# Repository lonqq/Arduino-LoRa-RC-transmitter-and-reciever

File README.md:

# Arduino based RC system
The ultimate DIY radio control system.
Remotely operate model airplanes, multicopters, boats, land vehicles, robots, or anything you can imagine.

## Main features
- 20 fully proportional RC channels, each channel encoded with 10 bits.
- Configurable RC channel output signal format.
- Update rate of 50x per second for all RC channels.
- Receiver binding, Adjustable RF power, Frequency hopping.
- Reverse, subtrim, endpoints, failsafe.
- Dual rates and expo, Custom curves, Flight modes.
- Powerful mixer system, Logical switches, Custom telemetry.
- Alarms, Warnings, Timers, etc.
- Intuitive user interface.
- Model memory. I2C eeprom and SD card supported.
- Model types, context-aware nomenclature; no need for land vehicles to have controls named after aircraft parts. 

## Hardware and Schematics
The schematics and related information can be found in the 'schematics' folder. 
The major components are as below.
- 1x Atmega2560 microcntroller, 2x Atmega328p microcontrollers.
- 2x SX1276/77/78/79 or RFM95 based Lora modules. However any module can possibly be used.
- 128x64 KS0108 based LCD. Any 128x64 LCD can however be used (provide own driver code).

## Compiling the firmware
The code compiles on arduino ide 1.8.x or later. The code is self-contained so doesn't require installing any libraries. 

## User Interface
Three buttons are used for navigation; Up, Select, Down. Long press Select to go Back.

## Topics
[Mixer](doc/mixer.md)
<br>[Custom curves](doc/custom_curves.md)
<br>[Logical switches](doc/logical_switches.md)
<br>[Telemetry](doc/telemetry.md)
<br>[Receiver binding and configuration](doc/receiver_config.md)

## Frequently Asked Questions
[Got a question or an issue? See the FAQ first.](doc/faq.md)

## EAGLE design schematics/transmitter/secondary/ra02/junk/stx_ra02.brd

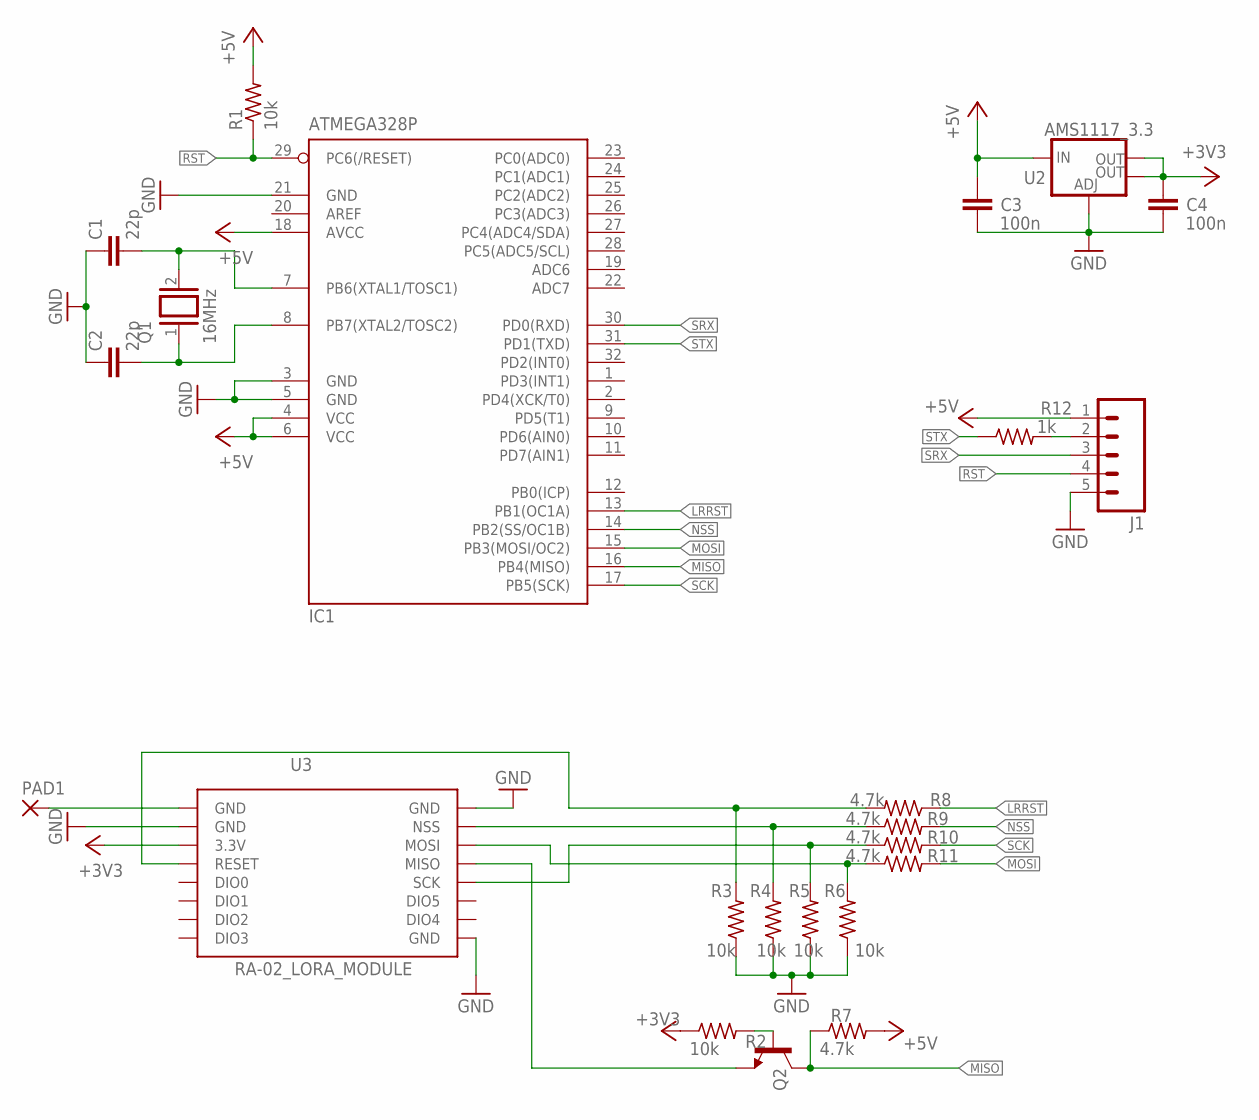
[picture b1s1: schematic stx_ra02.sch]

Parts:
C1, C2: 22p; C0805K
C3, C4: 100n; C0805K
IC1: ATMEGA328P; TQFP32-08
J1: M05PTH; 1X05
PAD1: 2,15/1,0
Q1: 16MHz; QS
Q2: BC817-16SMD; SOT23-BEC
R1, R2, R3, R4, R5, R6: 10k; R0805
R7, R8, R9, R10, R11: 4.7k; R0805
R12: 1k; R0805
U2: AMS1117_3.3; SOT223
U3: RA-02_LORA_MODULE; RA-02

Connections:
+3V3: C4.2, R2.1, U2.2 (OUT), U2.4 (OUT), U3.3.3V
+5V: C3.2, IC1.4 (VCC), IC1.6 (VCC), IC1.18 (AVCC), J1.1, R1.2, R7.2, U2.3 (IN)
GND: C1.1, C2.1, C3.1, C4.1, IC1.3 (GND), IC1.5 (GND), IC1.21 (GND), J1.5, R3.1, R4.1, R5.1, R6.1, U2.1 (ADJ), U3.GND@2 (GND), U3.GND@3 (GND), U3.GND@4 (GND)
LRRST: IC1.13 (PB1(OC1A)), R8.1
MISO: IC1.16 (PB4(MISO)), Q2.C, R7.1
MOSI: IC1.15 (PB3(MOSI/OC2)), R11.2
unnamed: C1.2, IC1.7 (PB6(XTAL1/TOSC1)), Q1.2
unnamed: J1.2, R12.2
unnamed: C2.2, IC1.8 (PB7(XTAL2/TOSC2)), Q1.1
unnamed: R3.2, R8.2, U3.RESET
unnamed: PAD1.1, U3.GND
unnamed: Q2.E, U3.MISO
unnamed: R4.2, R9.1, U3.NSS
unnamed: R5.2, R10.1, U3.SCK
unnamed: R6.2, R11.1, U3.MOSI
unnamed: Q2.B, R2.2
NSS: IC1.14 (PB2(SS/OC1B)), R9.2
RST: IC1.29 (PC6(/RESET)), J1.4, R1.1
SCK: IC1.17 (PB5(SCK)), R10.2
SRX: IC1.30 (PD0(RXD)), J1.3
STX: IC1.31 (PD1(TXD)), R12.1

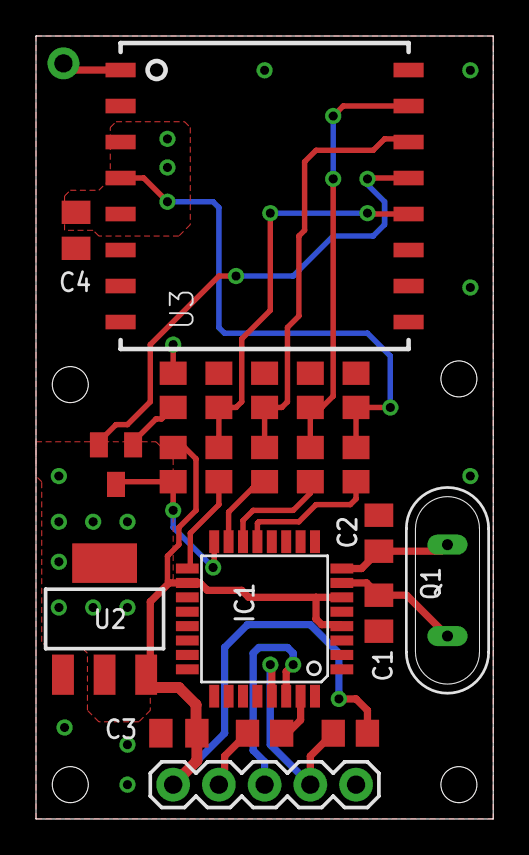
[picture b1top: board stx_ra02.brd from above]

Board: 2 copper layers, 25.4 x 43.5 mm, 23 parts (0 on the bottom side), 21 nets.

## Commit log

2023-11-02 Fixed crc includes for esp32

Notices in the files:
parts and their libraries:
SparkFun-PowerIC: Licensing: Creative Commons ShareAlike 4.0 International - https://creativecommons.org/licenses/by-sa/4.0
